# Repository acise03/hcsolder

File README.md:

# hcsolder

A cool use of LED lights that change depending on light in the room!
And a vibrating motor with varying intensity!

BOM:
1 battery + batter holder, 3 swtiches, 5 LED, 6 220 resistor, 2 potentiometer, 1 photoresistor, 1 mini motor disc, 1 transitor

Slack username: acise03

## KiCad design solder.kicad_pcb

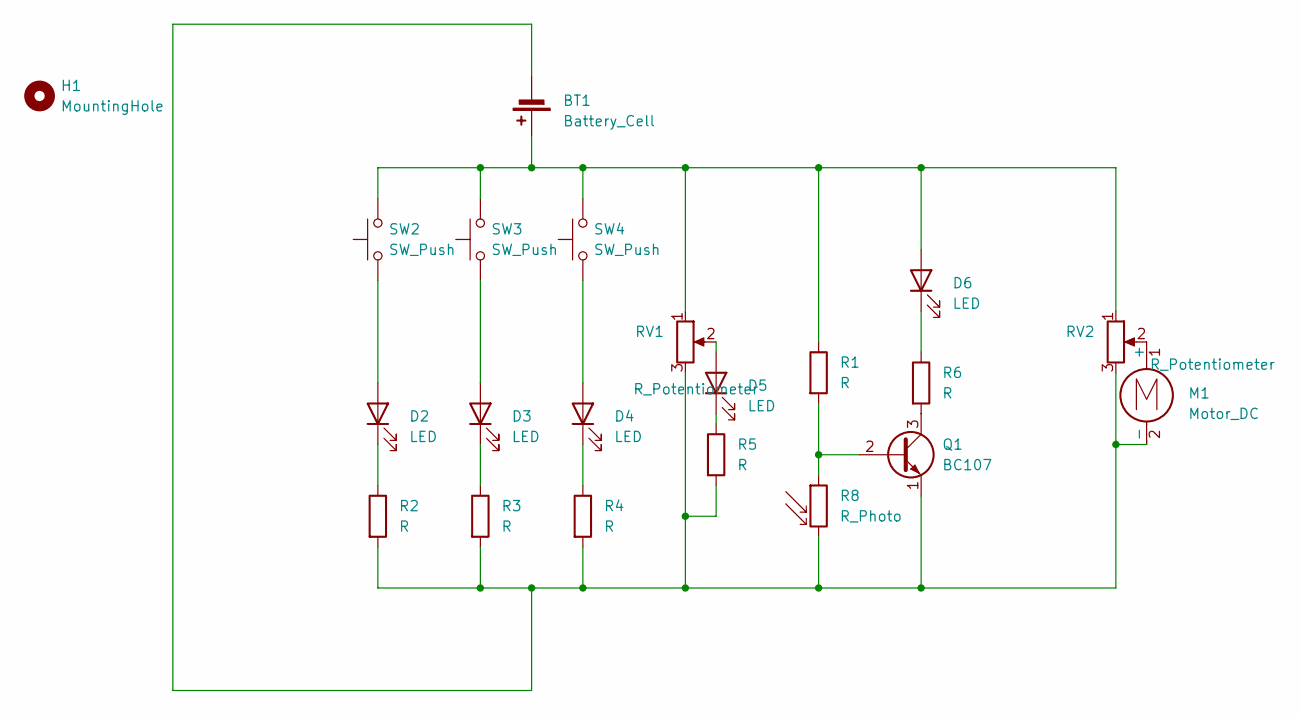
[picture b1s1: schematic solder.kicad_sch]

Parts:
BT1: Battery_Cell; BatteryHolder_Keystone_3034_1x20mm
D2, D3, D4, D5, D6: LED; LED_D5.0mm
H1: MountingHole; MountingHole_5mm
M1: Motor_DC; PinHeader_1x02_P2.54mm_Vertical
Q1: BC107; TO-18-3
R1, R2, R3, R4, R5, R6: R; R_Axial_DIN0207_L6.3mm_D2.5mm_P7.62mm_Horizontal
R8: R_Photo; R_LDR_5.1x4.3mm_P3.4mm_Vertical
RV1, RV2: R_Potentiometer; Potentiometer_Vishay_T73YP_Vertical
SW2, SW3, SW4: SW_Push; SW_PUSH_6mm

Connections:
unnamed: BT1.1 (+), D6.2 (A), R1.1, RV1.1, RV2.1, SW2.2, SW3.2, SW4.2
unnamed: BT1.2 (-), M1.2 (-), Q1.1 (E), R2.2, R3.2, R4.2, R5.2, R8.2, RV1.3, RV2.3
unnamed: D2.2 (A), SW2.1
unnamed: D2.1 (K), R2.1
unnamed: D3.2 (A), SW3.1
unnamed: D3.1 (K), R3.1
unnamed: D4.2 (A), SW4.1
unnamed: D4.1 (K), R4.1
unnamed: D5.2 (A), RV1.2
unnamed: D5.1 (K), R5.1
unnamed: D6.1 (K), R6.1
unnamed: M1.1 (+), RV2.2
unnamed: Q1.2 (B), R1.2, R8.1
unnamed: Q1.3 (C), R6.2

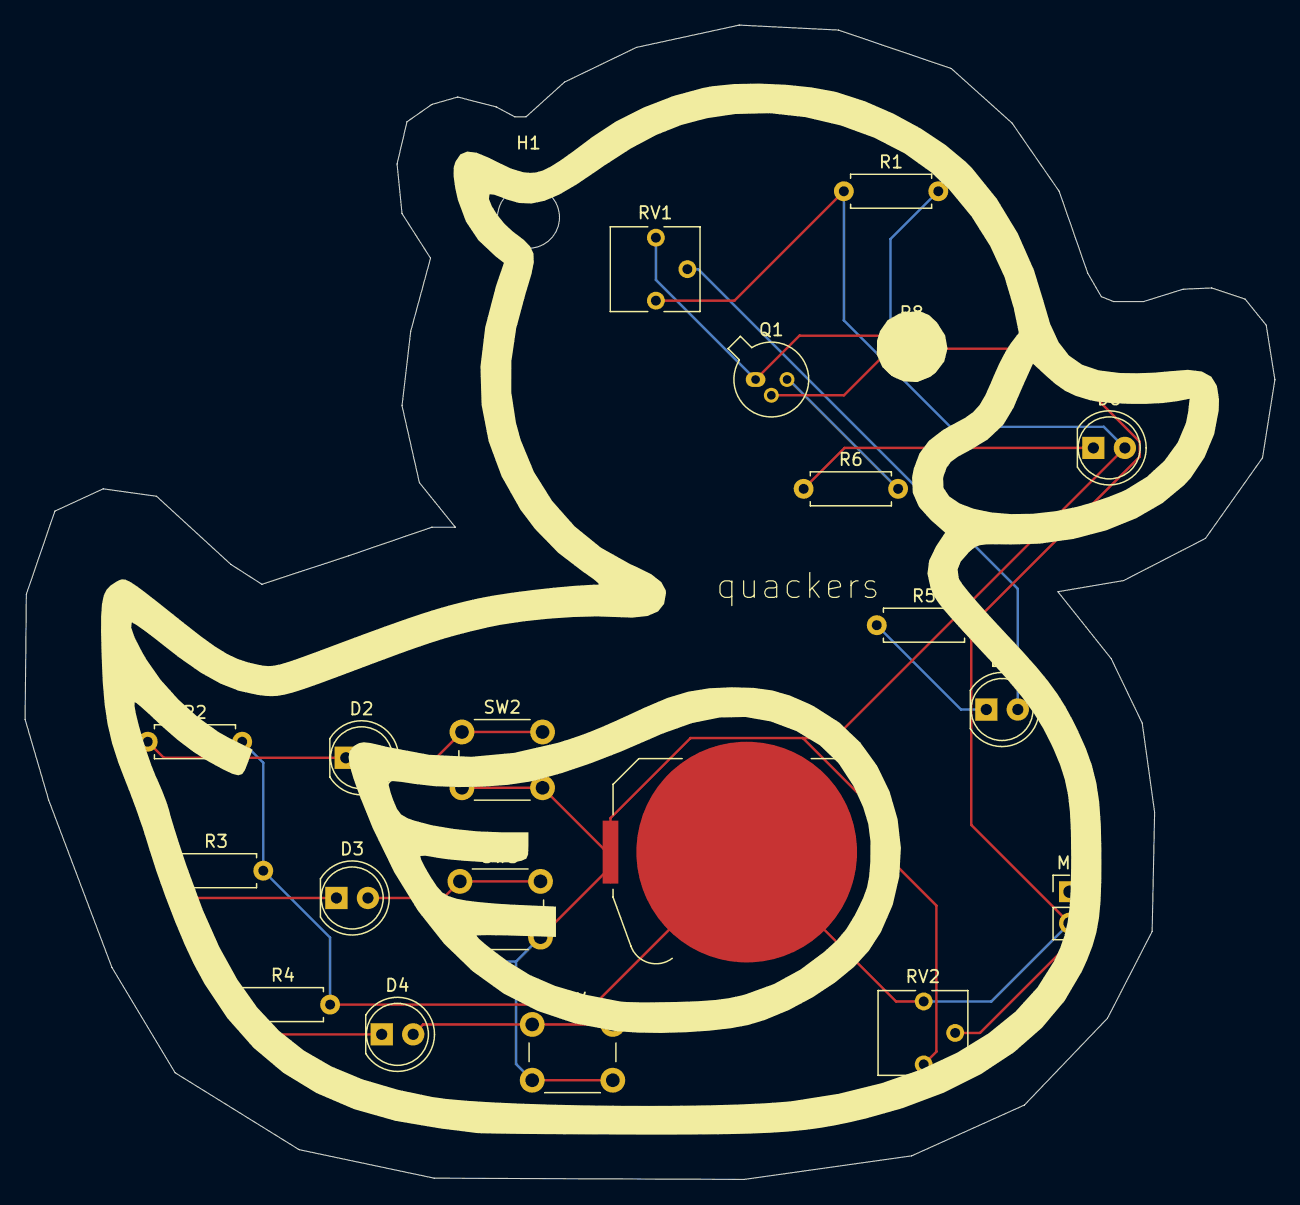
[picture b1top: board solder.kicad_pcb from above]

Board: 2 copper layers, 100.8 x 93.1 mm, 21 parts (0 on the bottom side), 14 nets.

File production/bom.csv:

Designator,Footprint,Quantity,Value,LCSC Part #
BT1,BatteryHolder_Keystone_3034_1x20mm,1,Battery_Cell,
"D2, D3, D4, D5, D6",LED_D5.0mm,5,LED,
M1,PinHeader_1x02_P2.54mm_Vertical,1,Motor_DC,
"R2, R3, R4, R5, R6",R_Axial_DIN0207_L6.3mm_D2.5mm_P7.62mm_Horizontal,5,R,
R8,R_LDR_5.1x4.3mm_P3.4mm_Vertical,1,R_Photo,
"RV1, RV2",Potentiometer_Vishay_T73YP_Vertical,2,R_Potentiometer,
"SW2, SW3, SW4",SW_PUSH_6mm,3,SW_Push,

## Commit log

2025-06-27 Add new solder backup and remove KiCad lock file
    Added a new backup archive for the solder project and deleted the obsolete KiCad PCB lock file.
